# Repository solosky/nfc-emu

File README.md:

# nfc-emu

这是一个可以模拟NTAG215的模拟器。
可以用来模拟Amiibo和门禁卡。
硬件理论上支持Mifare的卡片，但目前固件不支持。

## 功能

* 支持最多10张卡模拟
* 支持模拟Amiibo
* 4秒无响应自动断电

## PCB 

| RevA | RevB |
| --- | --- |
|  |  | 
| 可用 | 和RevA相比新增了CH343P串口芯片，可以直接通过USB下载固件。注意：RevB未能完整测试，使用慎重！！|

## 演示

## 固件编译和烧写

本固件是基于Ardunio框架实现的，所以固件烧写方法很类似。
主要分两步，第一步刷入bootloader, 第二步使用串口刷入固件。
bootloader只需要刷写一次即可，之后的固件更新可以直接用串口刷入新固件。

### 刷入Bootloader

需要的软件：progisp 
需要的硬件：USB ISP
* assets/optiboot_flash_atmega328p_UART0_115200_13560000L_B1.hex 刷入MCU中。
* 修改熔丝位：低位值：0xCE, 高位值：0xDE，扩展位：0xFF

连接左边标记为ISP的接口到USB ISP烧写器上，接线顺序如下：

CLK MOSI MISO RESET GND 

注意需要把电池安装上，在刷入bootloader过程中需要一直按住中键打开电源。

刷入步骤：
 1. 先点击 编程熔丝 后面的框，弹出熔丝对话框，点击读出按钮读出当前值，然后依次输入 低位值：0xCE, 高位值：0xDE，扩展位：0xFF，点击写入执行写入操作
 2. 点击文件 -> 调入flash, 选择assets/optiboot_flash_atmega328p_UART0_115200_13560000L_B1.hex，点击自动按钮写入bootloader

### 编译固件

首先需要下载 vscode, 安装platformio插件，并安装arduino框架。

因为用了非标准的13.56M的晶振，需要新建一个board。
在 C:\Users\{{用户名}}\.platformio\platforms\atmelavr\boards下面新建一个文件 ATmega328PNfcEmu.json， 内容如下：

```
{
  "build": {
    "core": "MiniCore",
    "extra_flags": "-DARDUINO_AVR_ATmega328P",
    "f_cpu": "13560000L",
    "mcu": "atmega328p",
    "variant": "standard"
  },
  "bootloader": {
    "led_pin": "B5"
  },
  "debug": {
    "simavr_target": "atmega328p",
    "avr-stub": {
      "speed": 115200
    }
  },
  "frameworks": [
    "arduino"
  ],
  "name": "ATmega328P/PA NFC EMU",
  "upload": {
    "maximum_ram_size": 2048,
    "maximum_size": 32768,
    "protocol": "arduino",
    "require_upload_port": true,
    "speed": 115200
  },
  "url": "https://www.microchip.com/wwwproducts/en/ATmega328P",
  "vendor": "Microchip"
}
```

使用vscode打开项目的fw文件夹，platformio插件会自动启动识别为一个platformio的项目。
点击编译按钮就可以完成编译。

### 刷入固件

刷入固件使用vscode的platformio插件完成。

#### RevA 

需要额外一个带DTR信号的USB转串口的模块，连接右边的UART接口按如下顺序连接USB串口模块。

+5V TXD RXD DTR GND 

注意：TXD连串口模块的RXD，RXD连串口模块的TXD。

#### RevB 

自带了的USB转串口模块，直接插上USB线，系统自动识别出串口设备。

#### 刷入步骤

刷入之前，修改platformio.ini中的 upload_port，monitor_port的值为设备的串口号。
点击上传按钮就可以下载固件到设备中。

## 支持的卡

硬件上支持14443-3A的低速卡，比如NTAG215, Mifare等常见卡。
软件层面目前只支持模拟NTAG215，Mifare卡暂时不支持。

## 功耗

目前使用中耗电量为22mA，CR2032勉强能使用，还需要进一步优化电路减少功耗。

因为设计了断电电路，不使用基本不耗电，使用时间取决于使用次数。

注意：一定要使用南孚的传应CR2032电池，其他电池不一定能提供这么大的放电电流！

## 写入TAG

可以用手机APP写入，也可以用PN532等NFC读写器写入。

### 使用手机APP写入

如果手机支持NFC，可以下载如下软件写入Amiibo:

iOS: AppleStore搜索Umiibo写入。
Umiibo是收费软件，但只需要6元RMB，没有应用内购买，很良心的APP的，强烈推荐购买。

Andriod: https://github.com/HiddenRamblings/TagMo/releases 下载最新版本的TAGMO安装。

如果以上都没有，可以购买PN532模块，然后安装Linux虚拟机，将PN532 USB设备接入虚拟机后，执行如下命令写入标签。

### 安装libnfc 

```
sudo apt update
sudo apt install libnfc-dev
```

### Amiibo写入
```
nfc-mfultralight w "SSB Zelda.bin" --full
NFC device: pn532 opened
1 ISO14443A passive target(s) found:
	040402cb5d6480
Using MIFARE Ultralight card with UID: 040402cb5d6480
WARNING: Tag is EV1 or NTAG - PASSWORD may be required
NTAG Type: NTAG215 (504 user bytes)
Checking if UL badge is DirectWrite...
 Original Block 0 (Pages 0-2): 0404028acb5d648072480000
 Original UID: 040402cb5d6480
 Attempt to write Block 0 (pages 0-2) ...
  Writing Page 0: 04 04 02 8a
  Writing Page 1: cb 5d 64 80
  Writing Page 2: 72 48 00 00
 Block 0 written successfully
Card is DirectWrite
Writing 135 pages |.......................................................................................................................................|
Done, 135 of 135 pages written (0 pages skipped, 0 pages failed).

```

默认固件所有标签都是空白的，需要用APP写入标签才能使用。

## 操作说明

* 关机状态下短按中键开机，电源指示灯亮起
* 开机状态下短按上，下键切换标签
* 开机状态下长按中键2秒以上重置标签，uid也会随机生成，标签指示灯会短闪两次
* 开机状态下靠近读卡器读取标签 

可以使用重置标签操作结合APP来无限刷Amiibo!

注意：写入和重置标签会产生Flash的写入操作，一般来说Flash的写入操作是有次数限制的，按ATMEGA328p的手册来说，每扇区至少有10000次写入寿命，所以每个标签的至少能刷写10000次左右（重置和写入算两次操作），超过这个次数当前标签的数据可能永久无法写入。

后续可以考虑实现写均衡来充分利用剩余未使用的空间来提高标签的写入次数。
 
# 感谢 

此项目是移植 [Simple NFC](https://github.com/Nonannet/simple-nfc)，主要的模拟代码来源SimpleNFC，感谢 @Nonannet 提供的代码，非常棒的实现！

# 欢迎加群讨论 

QQ群：109761876

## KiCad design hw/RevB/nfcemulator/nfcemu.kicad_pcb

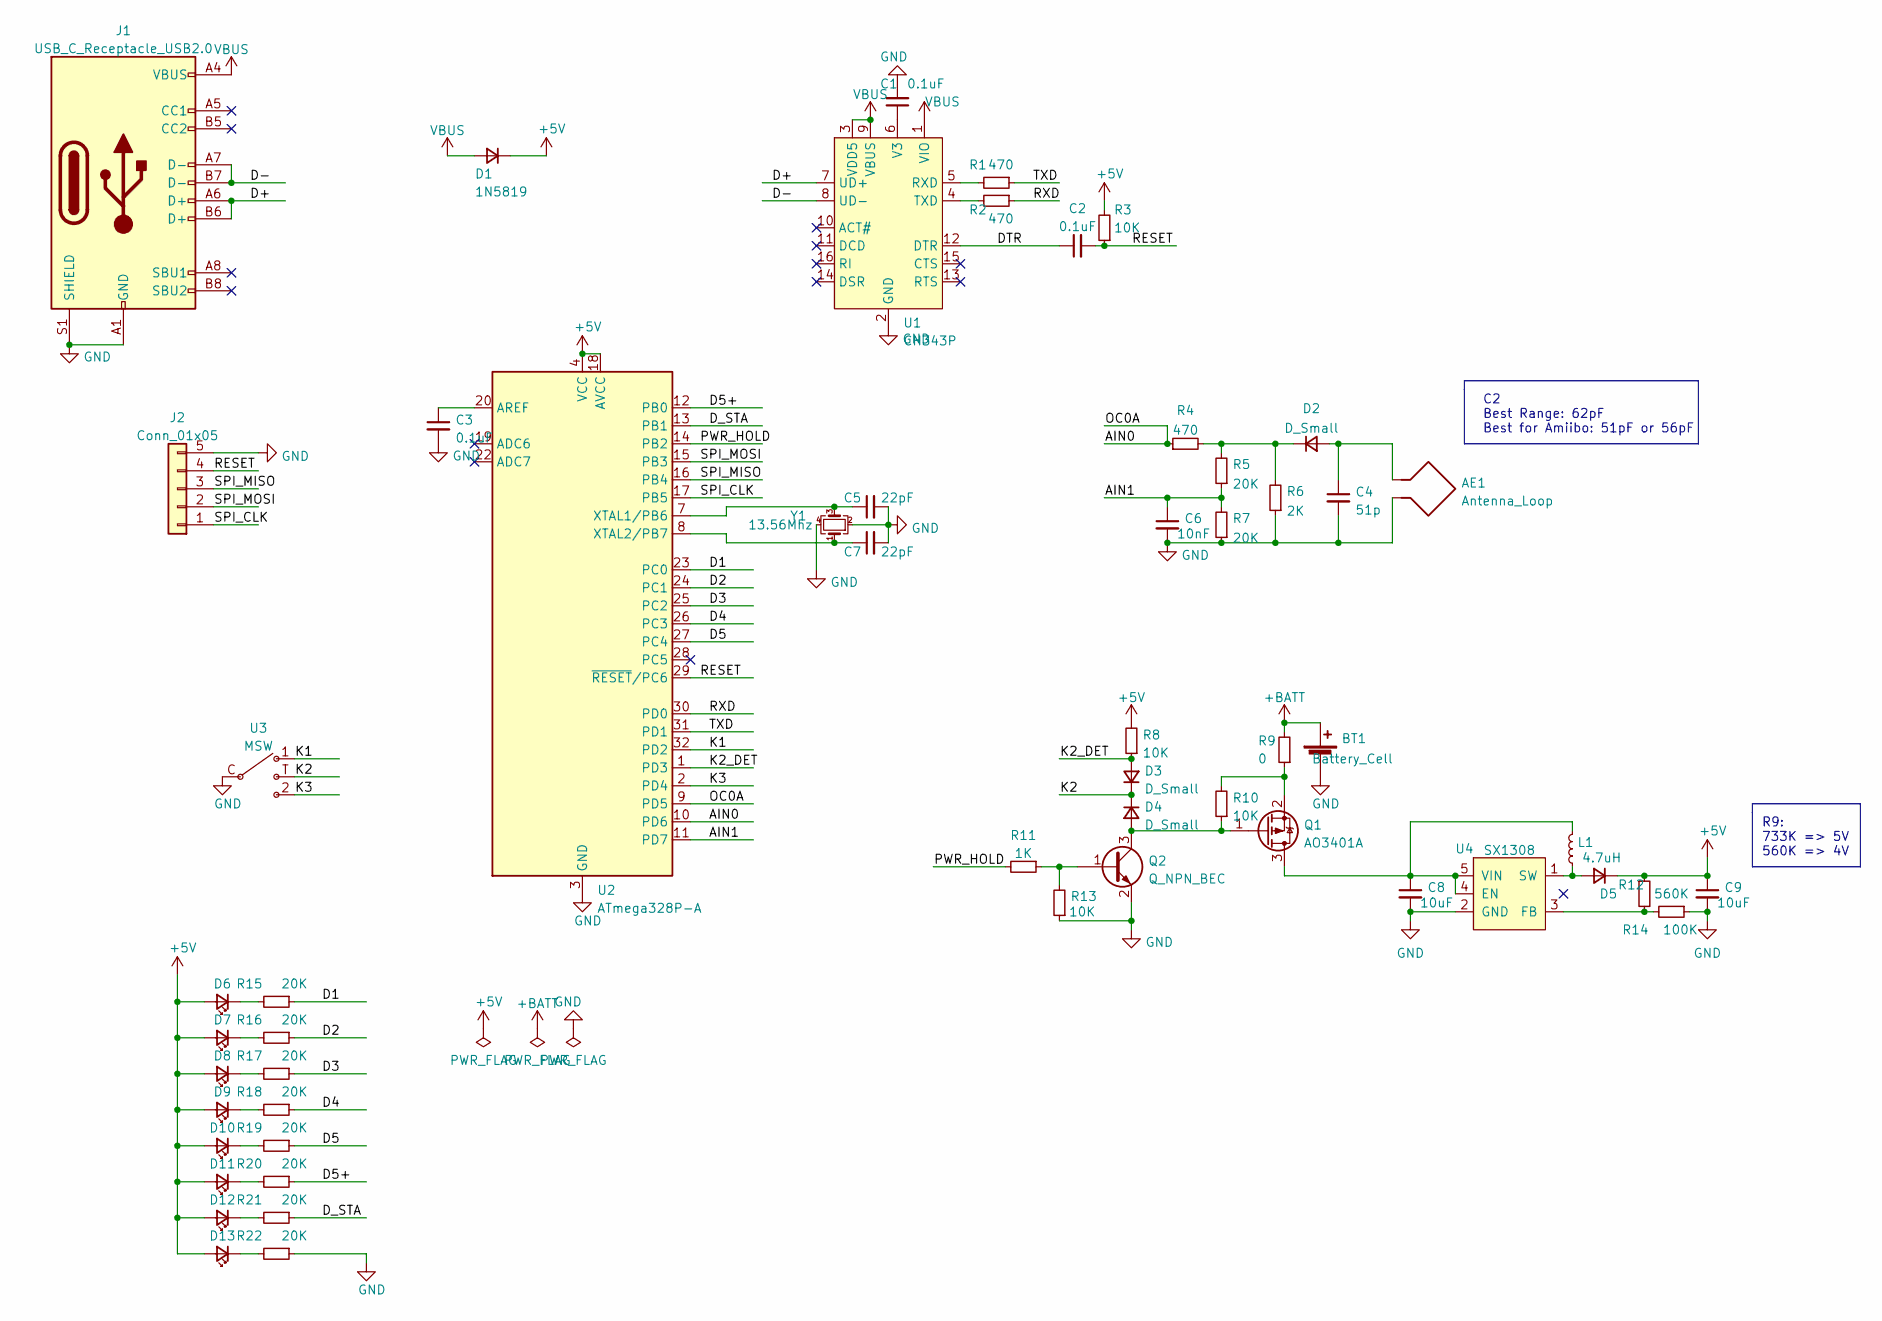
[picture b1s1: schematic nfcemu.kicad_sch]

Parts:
AE1: Antenna_Loop; NFC_ANT2
BT1: Battery_Cell; BatteryHolder_Keystone_3002_1x2032
C1, C2, C3: 0.1uF; C_0402_1005Metric
C4: 51p; C_0402_1005Metric
C5, C7: 22pF; C_0402_1005Metric
C6: 10nF; C_0402_1005Metric
C8, C9: 10uF; C_0603_1608Metric
D1: 1N5819; D_SOD-323
D2, D3, D4, D5: D_Small; D_SOD-323
D6, D7, D8, D9, D10, D11, D12, D13: LED_Small; LED_0402_1005Metric
J1: USB_C_Receptacle_USB2.0; USB_C_Receptacle_HRO_TYPE-C-31-M-12
J2: Conn_01x05; PinHeader_1x05_P1.27mm_Vertical
L1: 4.7uH; L_0805_2012Metric
Q1: AO3401A; SOT-23
Q2: Q_NPN_BEC; SOT-23
R1, R2, R4: 470; R_0402_1005Metric
R3, R8, R10, R13: 10K; R_0402_1005Metric
R5, R7, R15, R16, R17, R18, R19, R20, R21, R22: 20K; R_0402_1005Metric
R6: 2K; R_0402_1005Metric
R9: 0; R_0402_1005Metric
R11: 1K; R_0402_1005Metric
R12: 560K; R_0402_1005Metric
R14: 100K; R_0402_1005Metric
U1: CH343P; QFN-16-1EP_3x3mm_P0.5mm_EP1.45x1.45mm
U2: ATmega328P-A; TQFP-32_7x7mm_P0.8mm
U3: MSW
U4: SX1308; TSOT-23-6
Y1: 13.56Mhz; Crystal_SMD_3225-4Pin_3.2x2.5mm

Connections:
+5V: C9.1, D1.1 (K), D5.1 (K), D6.2 (A), D7.2 (A), D8.2 (A), D9.2 (A), D10.2 (A), D11.2 (A), D12.2 (A), D13.2 (A), R3.2, R8.2, R12.1, U2.4 (VCC), U2.6 (VCC), U2.18 (AVCC)
+BATT: BT1.1 (+), R9.2
/AIN0: R4.1, U2.9 (PD5), U2.10 (PD6)
/AIN1: C6.1, R5.1, R7.2, U2.11 (PD7)
/D1: R15.1, U2.23 (PC0)
/D2: R16.1, U2.24 (PC1)
/D3: R17.1, U2.25 (PC2)
/D4: R18.1, U2.26 (PC3)
/D5: R19.1, U2.27 (PC4)
/D5+: R20.1, U2.12 (PB0)
/D+: J1.A6 (D+), J1.B6 (D+), U1.7 (UD+)
/D-: J1.A7 (D-), J1.B7 (D-), U1.8 (UD-)
/DTR: C2.1, U1.12 (DTR)
/D_STA: R21.1, U2.13 (PB1)
/K1: U2.32 (PD2), U3.1
/K2: D3.1 (K), D4.1 (K), U3.T
/K2_DET: D3.2 (A), R8.1, U2.1 (PD3)
/K3: U2.2 (PD4), U3.2
/PWR_HOLD: R11.2, U2.14 (PB2)
/RESET: C2.2, J2.4, R3.1, U2.29 (~RESET/PC6)
/RXD: R2.1, U2.30 (PD0)
/SPI_CLK: J2.1, U2.17 (PB5)
/SPI_MISO: J2.3, U2.16 (PB4)
/SPI_MOSI: J2.2, U2.15 (PB3)
/TXD: R1.1, U2.31 (PD1)
GND: AE1.1, BT1.2 (-), C1.2, C3.2, C4.2, C5.2, C6.2, C7.2, C8.2, C9.2, J1.A1 (GND), J1.A12 (GND), J1.B1 (GND), J1.B12 (GND), J1.S1 (SHIELD), J2.5, Q2.2 (E), R6.1, R7.1, R13.1, R14.1, R22.1, U1.2 (GND), U1.17 (EP), U2.3 (GND), U2.5 (GND), U2.21 (GND), U3.C, U4.2 (GND), Y1.2, Y1.4
unnamed: AE1.2, C4.1, D2.2 (A)
unnamed: C1.1, U1.6 (V3)
unnamed: C3.1, U2.20 (AREF)
unnamed: C5.1, U2.7 (XTAL1/PB6), Y1.3
unnamed: C7.1, U2.8 (XTAL2/PB7), Y1.1
unnamed: C8.1, L1.2, Q1.3 (D), U4.4 (EN), U4.5 (VIN)
unnamed: D2.1 (K), R4.2, R5.2, R6.2
unnamed: D4.2 (A), Q1.1 (G), Q2.3 (C), R10.1
unnamed: D5.2 (A), L1.1, U4.1 (SW)
unnamed: D6.1 (K), R15.2
unnamed: D7.1 (K), R16.2
unnamed: D8.1 (K), R17.2
unnamed: D9.1 (K), R18.2
unnamed: D10.1 (K), R19.2
unnamed: D11.1 (K), R20.2
unnamed: D12.1 (K), R21.2
unnamed: D13.1 (K), R22.2
unnamed: Q1.2 (S), R9.1, R10.2
unnamed: Q2.1 (B), R11.1, R13.2
unnamed: R1.2, U1.5 (RXD)
unnamed: R2.2, U1.4 (TXD)
unnamed: R12.2, R14.2, U4.3 (FB)
unnamed: U3.5, U3.6, U3.7, U3.8
VBUS: D1.2 (A), J1.A4 (VBUS), J1.A9 (VBUS), J1.B4 (VBUS), J1.B9 (VBUS), U1.1 (VIO), U1.3 (VDD5), U1.9 (VBUS)

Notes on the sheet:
R9: 733K => 5V 560K => 4V
C2 Best Range: 62pF Best for Amiibo: 51pF or 56pF

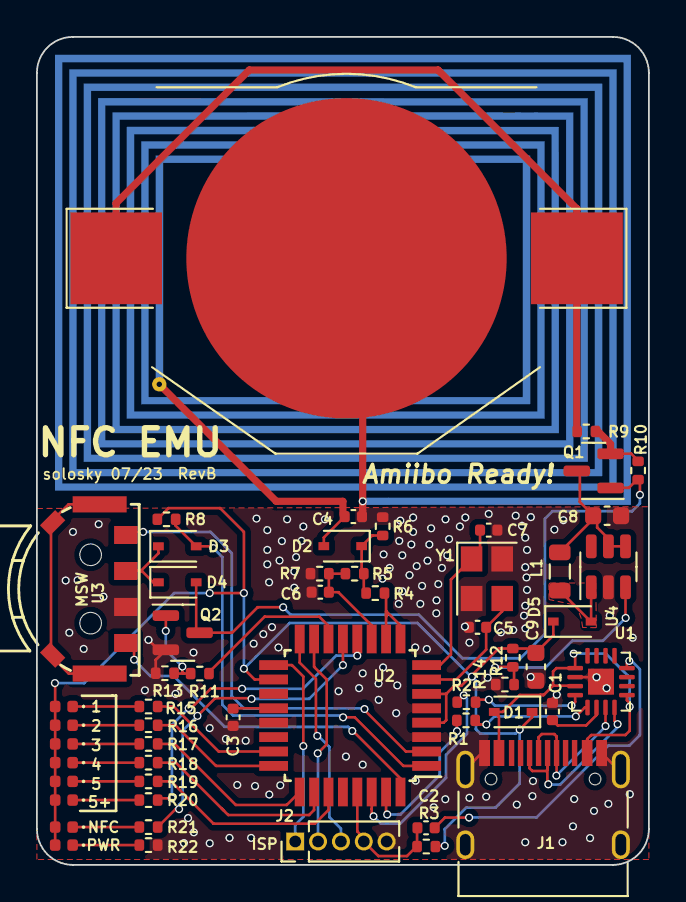
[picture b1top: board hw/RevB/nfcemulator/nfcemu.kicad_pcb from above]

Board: 2 copper layers, 34.0 x 46.0 mm, 56 parts (1 on the bottom side), 50 nets.

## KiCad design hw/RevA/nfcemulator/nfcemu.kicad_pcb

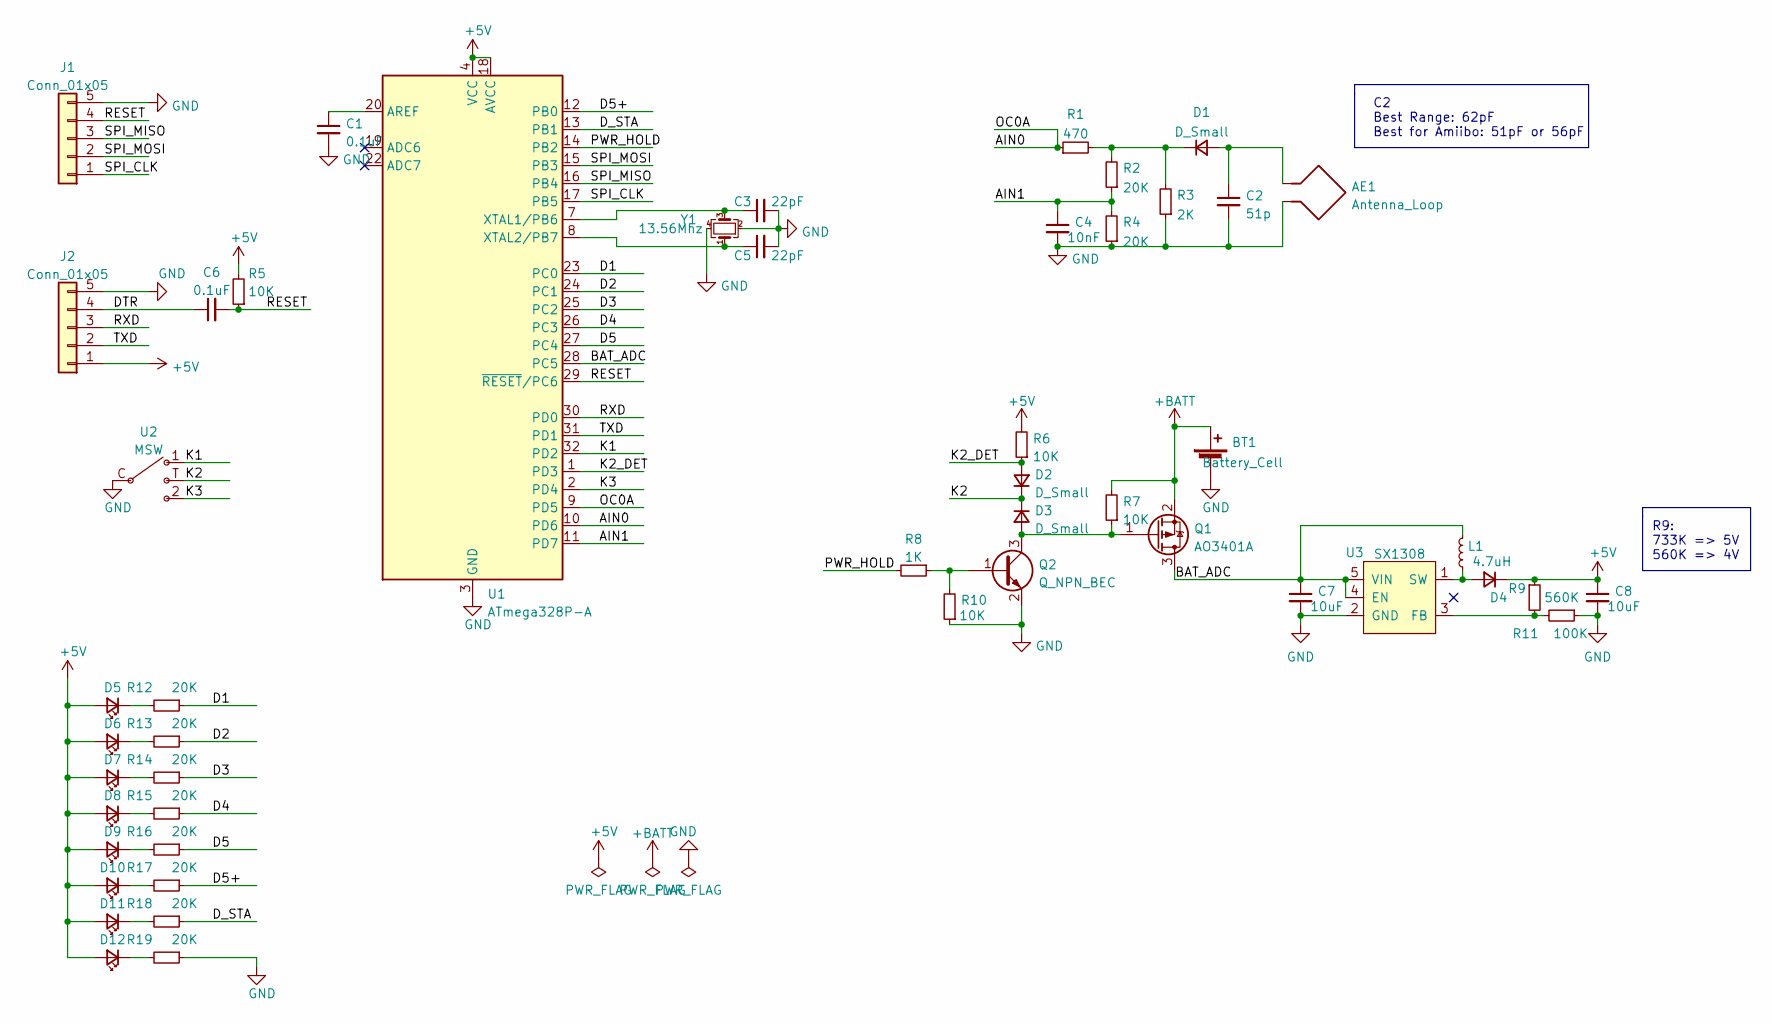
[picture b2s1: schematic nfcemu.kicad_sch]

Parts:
AE1: Antenna_Loop; NFC_ANT2
BT1: Battery_Cell; BatteryHolder_Keystone_3002_1x2032
C1, C6: 0.1uF; C_0402_1005Metric
C2: 51p; C_0402_1005Metric
C3, C5: 22pF; C_0402_1005Metric
C4: 10nF; C_0402_1005Metric
C7, C8: 10uF; C_0603_1608Metric
D1, D2, D3, D4: D_Small; D_SOD-323
D5, D6, D7, D8, D9, D10, D11, D12: LED_Small; LED_0402_1005Metric
J1, J2: Conn_01x05; PinHeader_1x05_P1.27mm_Vertical
L1: 4.7uH; L_0805_2012Metric
Q1: AO3401A; SOT-23
Q2: Q_NPN_BEC; SOT-23
R1: 470; R_0402_1005Metric
R2, R4, R12, R13, R14, R15, R16, R17, R18, R19: 20K; R_0402_1005Metric
R3: 2K; R_0402_1005Metric
R5, R6, R7, R10: 10K; R_0402_1005Metric
R8: 1K; R_0402_1005Metric
R9: 560K; R_0402_1005Metric
R11: 100K; R_0402_1005Metric
U1: ATmega328P-A; TQFP-32_7x7mm_P0.8mm
U2: MSW
U3: SX1308; TSOT-23-6
Y1: 13.56Mhz; Crystal_SMD_3225-4Pin_3.2x2.5mm

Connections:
+5V: C8.1, D4.1 (K), D5.2 (A), D6.2 (A), D7.2 (A), D8.2 (A), D9.2 (A), D10.2 (A), D11.2 (A), D12.2 (A), J2.1, R5.2, R6.2, R9.1, U1.4 (VCC), U1.6 (VCC), U1.18 (AVCC)
+BATT: BT1.1 (+), Q1.2 (S), R7.2
/AIN0: R1.1, U1.9 (PD5), U1.10 (PD6)
/AIN1: C4.1, R2.1, R4.2, U1.11 (PD7)
/BAT_ADC: C7.1, L1.2, Q1.3 (D), U1.28 (PC5), U3.4 (EN), U3.5 (VIN)
/D1: R12.1, U1.23 (PC0)
/D2: R13.1, U1.24 (PC1)
/D3: R14.1, U1.25 (PC2)
/D4: R15.1, U1.26 (PC3)
/D5: R16.1, U1.27 (PC4)
/D5+: R17.1, U1.12 (PB0)
/DTR: C6.1, J2.4
/D_STA: R18.1, U1.13 (PB1)
/K1: U1.32 (PD2), U2.1
/K2: D2.1 (K), D3.1 (K), U2.T
/K2_DET: D2.2 (A), R6.1, U1.1 (PD3)
/K3: U1.2 (PD4), U2.2
/PWR_HOLD: R8.2, U1.14 (PB2)
/RESET: C6.2, J1.4, R5.1, U1.29 (~RESET/PC6)
/RXD: J2.3, U1.30 (PD0)
/SPI_CLK: J1.1, U1.17 (PB5)
/SPI_MISO: J1.3, U1.16 (PB4)
/SPI_MOSI: J1.2, U1.15 (PB3)
/TXD: J2.2, U1.31 (PD1)
GND: AE1.1, BT1.2 (-), C1.2, C2.2, C3.2, C4.2, C5.2, C7.2, C8.2, J1.5, J2.5, Q2.2 (E), R3.1, R4.1, R10.1, R11.1, R19.1, U1.3 (GND), U1.5 (GND), U1.21 (GND), U2.C, U3.2 (GND), Y1.2, Y1.4
unnamed: AE1.2, C2.1, D1.2 (A)
unnamed: C1.1, U1.20 (AREF)
unnamed: C3.1, U1.7 (XTAL1/PB6), Y1.3
unnamed: C5.1, U1.8 (XTAL2/PB7), Y1.1
unnamed: D1.1 (K), R1.2, R2.2, R3.2
unnamed: D3.2 (A), Q1.1 (G), Q2.3 (C), R7.1
unnamed: D4.2 (A), L1.1, U3.1 (SW)
unnamed: D5.1 (K), R12.2
unnamed: D6.1 (K), R13.2
unnamed: D7.1 (K), R14.2
unnamed: D8.1 (K), R15.2
unnamed: D9.1 (K), R16.2
unnamed: D10.1 (K), R17.2
unnamed: D11.1 (K), R18.2
unnamed: D12.1 (K), R19.2
unnamed: Q2.1 (B), R8.1, R10.2
unnamed: R9.2, R11.2, U3.3 (FB)
unnamed: U2.5, U2.6, U2.7, U2.8

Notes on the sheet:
R9: 733K => 5V 560K => 4V
C2 Best Range: 62pF Best for Amiibo: 51pF or 56pF

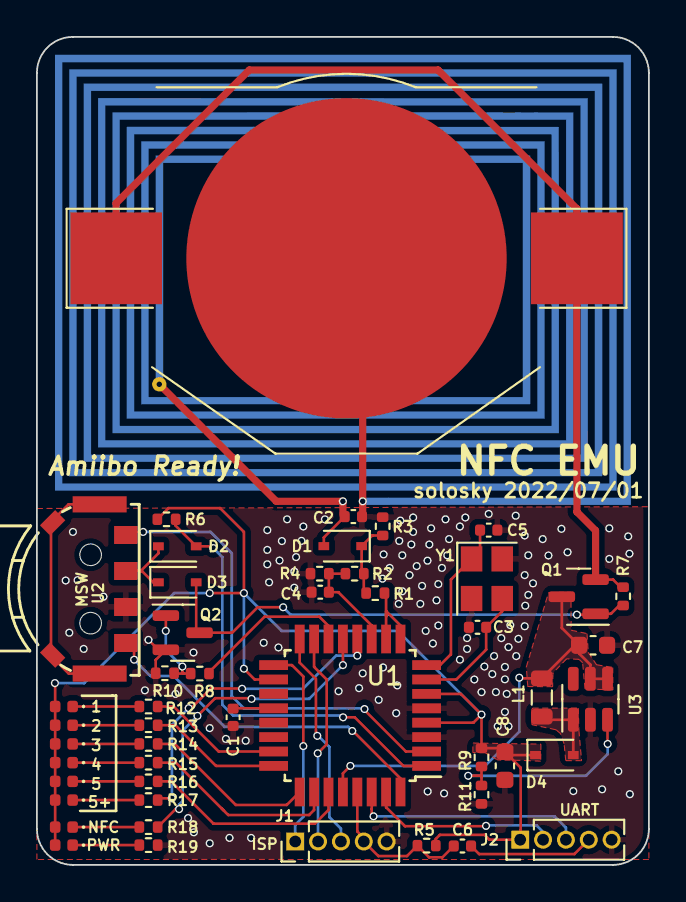
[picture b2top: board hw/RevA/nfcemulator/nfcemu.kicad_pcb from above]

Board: 2 copper layers, 34.0 x 46.0 mm, 50 parts (1 on the bottom side), 43 nets.

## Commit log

2022-07-10 init commit
2022-07-11 update images
2022-07-11 add amiibo demo1
2022-07-15 improve docs
2022-07-17 fix power off failed issue
2022-09-15 add RevB: onboard UART chip ch343p
2022-09-16 更新readme, 删除默认的卡片
2022-09-18 新增标签重置功能
2022-09-18 更新README
2022-09-19 修复长按可能重启问题和更新readme
